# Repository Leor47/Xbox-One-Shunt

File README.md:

---

# Xbox One Bliss Hack Efuse Side-Channel Current Monitor (TLV3201)

# *THIS IS COMPLETELY UNTESTED AND WAS CREATED WITH LOADS OF HELP USE AS A REFERENCE ONLY*

## Hardware

### Schematic

### PCB Layout

### PCB Render

This project implements a small analog front-end designed to detect short current spikes on a low-voltage rail and convert them into a clean digital timing signal suitable for capture by a microcontroller.

The circuit measures current through a shunt resistor, and feeds the signal into a high-speed comparator that generates a logic pulse.

The digital output can be captured by a microcontroller (for example a **Teensy**) for precise timing measurements.

# Credits

The PCB layout was created by another contributor.

This repository contains the schematic, design files, and documentation for the circuit.

---

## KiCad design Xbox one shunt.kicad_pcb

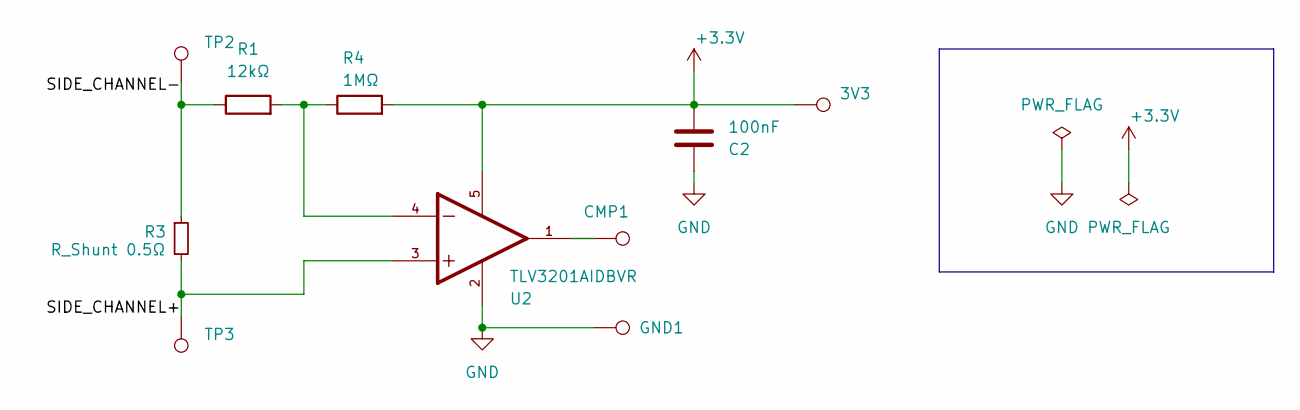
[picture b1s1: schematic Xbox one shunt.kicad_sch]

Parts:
3V3: TestPoint; TestPoint_Pad_D1.5mm
C2: 100nF; C_0603_1608Metric
CMP1: TestPoint; TestPoint_Pad_D1.5mm
GND1: TestPoint; TestPoint_Pad_D1.5mm
R1: 12kΩ; R_0603_1608Metric
R3: R_Shunt 0.5Ω; R_0603_1608Metric
R4: 1MΩ; R_0603_1608Metric
TP2, TP3: TestPoint; TestPoint_Pad_D1.5mm
U2: TLV3201AIDBVR; PARTREV B

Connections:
+3.3V: 3V3.1, C2.2, R4.2, U2.5
/SIDE_CHANNEL+: R3.2, TP3.1, U2.3
/SIDE_CHANNEL-: R1.1, R3.1, TP2.1
GND: C2.1, GND1.1, U2.2
unnamed: CMP1.1, U2.1
unnamed: R1.2, R4.1, U2.4

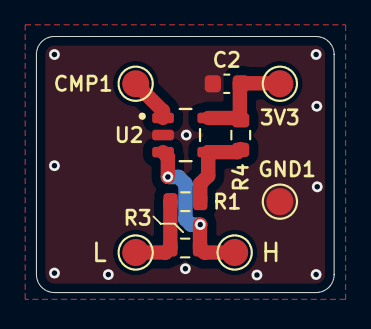
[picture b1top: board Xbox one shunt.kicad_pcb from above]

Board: 2 copper layers, 16.5 x 14.2 mm, 10 parts (0 on the bottom side), 6 nets.

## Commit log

2026-03-16 First Commit
    Small breakout board that should help read the e-fuse side channel on the Xbox One Bliss hack
2026-03-16 fixed gitignore
2026-03-16 Added images
2026-03-16 Add README for Xbox One Bliss Hack project
    Add detailed documentation for Xbox One Bliss Hack efuse current monitor project, including hardware schematics, signal processing, and layout guidelines.
2026-03-16 Fix typo in .gitignore for Excel files
2026-03-19 added a U.FL SMT conector for an osciloscope
2026-03-20 pcb and sch fixes
    Replaced TLV3201AIDCKR (SC70-5) which was using an SOT-23-5 footprint with a TLV3201AIDBVR (same specs and correct footprint)
    Updated schematic and PCB for above change
    Added Libraries directory and applied to project
    Edited symbols
    Fixed silks
    Added 3D models
2026-03-31 v2
    v2 after initial testing
    clean drc
2026-03-31 merge fix
    last commit broke
2026-03-31 Update README for clarity and accuracy
    Removed reference to INA181 in the title and updated hardware description for clarity. Condensed sections related to current sensing, signal amplification, and comparator threshold.
2026-04-17 fixed shunt value and resistor value
2026-04-17 updated images
2026-04-17 Replace old images with version 2 in README
    Updated images for schematic, PCB layout, and render.
